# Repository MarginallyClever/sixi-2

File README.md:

# Sixi 2 Robot Arm

Sixi 2 is an open source industrial robot arm.  It is designed with six degrees of freedom and can hold 2kg at 80cm.
Some examples of it in action:

## Videos

* https://www.instagram.com/p/B56L99UnWkN/
* https://www.instagram.com/p/B6L7YMTnthS/
* https://www.instagram.com/p/B6jtXw5HbRo/

## Motivation

3D printers can print parts for themselves, but they cannot self-assemble.  The long goal of the Sixi is to build a machine that can assemble copies of itself.

When 3D printers were closed source, they started at $10k.  Makerbot and Prusa changed the game by bringing high quality open source 3D printers down to $2k.  Marginally Clever Robots, Ltd. aims to be the Prusa of robot arms.

## This repository 

This repository contains:

* The STL files from the stable version
* The bill of materials (BOM.csv)
* Issue tickets specifically related to the hardware.
* ROS package.

This repository does NOT contain:

* Assembly instructions + software guide: https://mcr.dozuki.com/c/Sixi_2_kit_Asssembly
* Robot Overlord app to simulate, drive, and test Sixi: https://github.com/MarginallyClever/Robot-Overlord-App
* Makelangelo Firmware in the Sixi's brain: https://github.com/MarginallyClever/Makelangelo-firmware

## Notes

The BOM.csv lists all the parts in the kit, most of which are off-the-shelf.  Some parts are manufactured.
	
	[LSR] laser cut
	[CNC] metal cut on a CNC mill
	[3D]  3D printed PLA plastic.

All the 3D printable parts were produced on a Prusa MK3S.  Parts are carefully designed to have a minimum of support material cleaning.
Please see STLs/STLPrintSettings.csv for recommended layer height, speed, color, etc.

The Sixi has no glue because we like operations that can be undone.

## Collaborate

We love collaborating!  Let's make great things happen together.

* Discuss the project in our Discord: https://discord.gg/p2NRZFxXbh
* For a link to the Fusion files, become one of our Patreon supporters: https://www.patreon.com/imakerobots
* See also the ROS.org wiki page: https://wiki.ros.org/Robots/Sixi

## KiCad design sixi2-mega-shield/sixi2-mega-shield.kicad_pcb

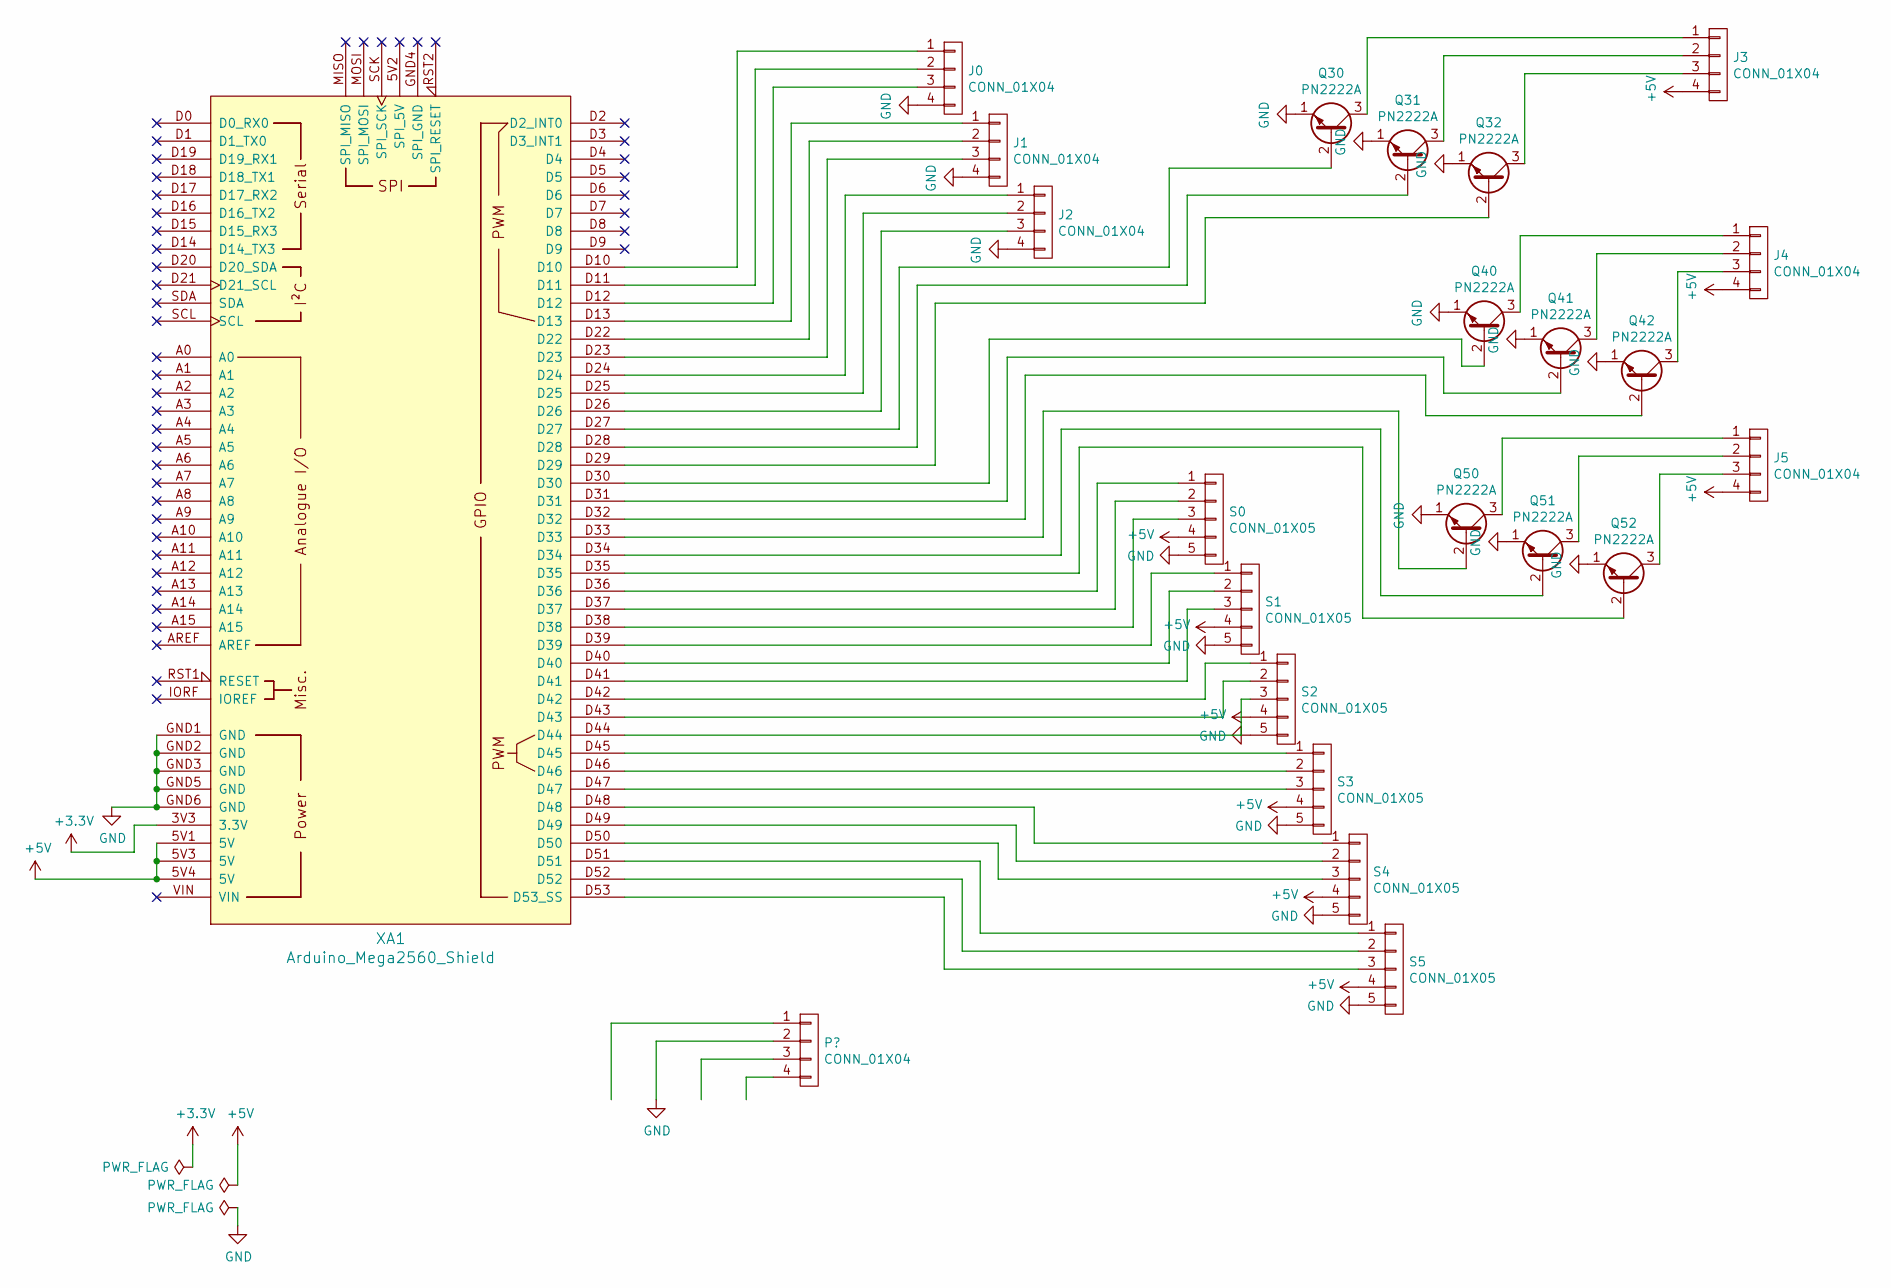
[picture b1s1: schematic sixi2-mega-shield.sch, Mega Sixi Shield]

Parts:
J0, J1, J2, J3, J4, J5: CONN_01X04; JST_XH_B4B-XH-A_1x04_P2.50mm_Vertical
Q30, Q31, Q32, Q40, Q41, Q42, Q50, Q51, Q52: PN2222A; TO-92_Inline_Wide
S0, S1, S2, S3, S4, S5: CONN_01X05; JST_XH_B5B-XH-A_1x05_P2.50mm_Vertical
XA1: Arduino_Mega2560_Shield

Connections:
+5V: J3.4, J4.4, J5.4, S0.4, S1.4, S2.4, S3.4, S4.4, S5.4, XA1.5V1 (5V), XA1.5V3 (5V), XA1.5V4 (5V)
GND: J0.4, J1.4, J2.4, Q30.1 (E), Q31.1 (E), Q32.1 (E), Q40.1 (E), Q41.1 (E), Q42.1 (E), Q50.1 (E), Q51.1 (E), Q52.1 (E), S0.5, S1.5, S2.5, S3.5, S4.5, S5.5, XA1.GND1 (GND), XA1.GND2 (GND), XA1.GND3 (GND), XA1.GND5 (GND), XA1.GND6 (GND)
unnamed: J0.1, XA1.D10
unnamed: J0.2, XA1.D11
unnamed: J0.3, XA1.D12
unnamed: J1.1, XA1.D13
unnamed: J1.2, XA1.D22
unnamed: J1.3, XA1.D23
unnamed: J2.1, XA1.D24
unnamed: J2.2, XA1.D25
unnamed: J2.3, XA1.D26
unnamed: J3.1, Q30.3 (C)
unnamed: J3.2, Q31.3 (C)
unnamed: J3.3, Q32.3 (C)
unnamed: J4.1, Q40.3 (C)
unnamed: J4.2, Q41.3 (C)
unnamed: J4.3, Q42.3 (C)
unnamed: J5.1, Q50.3 (C)
unnamed: J5.2, Q51.3 (C)
unnamed: J5.3, Q52.3 (C)
unnamed: Q30.2 (B), XA1.D27
unnamed: Q31.2 (B), XA1.D28
unnamed: Q32.2 (B), XA1.D29
unnamed: Q40.2 (B), XA1.D30
unnamed: Q41.2 (B), XA1.D31
unnamed: Q42.2 (B), XA1.D32
unnamed: Q50.2 (B), XA1.D33
unnamed: Q51.2 (B), XA1.D34
unnamed: Q52.2 (B), XA1.D35
unnamed: S0.1, XA1.D36
unnamed: S0.2, XA1.D37
unnamed: S0.3, XA1.D38
unnamed: S1.1, XA1.D39
unnamed: S1.2, XA1.D40
unnamed: S1.3, XA1.D41
unnamed: S2.1, XA1.D42
unnamed: S2.2, XA1.D43
unnamed: S2.3, XA1.D44
unnamed: S3.1, XA1.D45
unnamed: S3.2, XA1.D46
unnamed: S3.3, XA1.D47
unnamed: S4.1, XA1.D48
unnamed: S4.2, XA1.D49
unnamed: S4.3, XA1.D50
unnamed: S5.1, XA1.D51
unnamed: S5.2, XA1.D52
unnamed: S5.3, XA1.D53 (D53_SS)

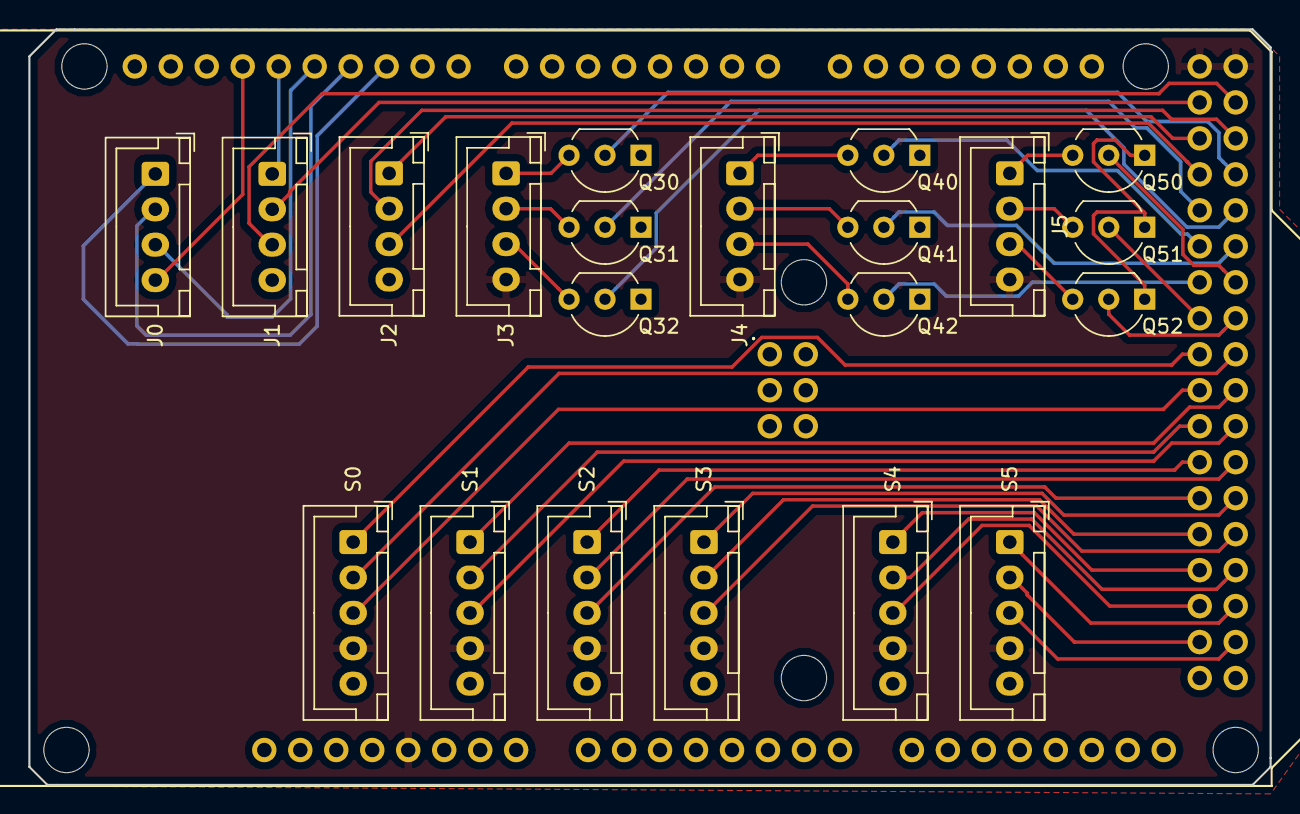
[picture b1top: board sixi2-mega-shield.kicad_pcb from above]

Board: 2 copper layers, 87.6 x 53.3 mm, 22 parts (0 on the bottom side), 47 nets.

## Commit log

2018-12-01 initial commit
    hooray!
2018-12-02 added tools
2018-12-04 updated j3 sensor mount to include letters on part models
2018-12-10 Fix for #1 + added discord link
2018-12-10 update 3Bb, added hole cut pattern for PVC tube.
2018-12-10 fixed formatting
2018-12-10 added image description
2018-12-10 formatting
2019-04-05 Update for 2019-04-04.
    Only the kicad sixi2-mega-shield is currently valid. All other files should be treated as suspect. We are working out a new process in the workshop so that they will stay up to date all the time.
2019-05-23 removed old picture.
2019-09-02 added graphs
2020-02-14 Updated STL files
2020-02-24 STL export finalized, printsetting added
2020-02-26 csv version added, lsr dxf deleted,
2020-02-26 update readme and BOM
2020-02-26 added 089
2020-03-02 Turned parts for printing
2020-03-03 shoulder cut wasn't done correctly, fixed
2020-03-03 ElbowGB 3mm Roller Fixed
2020-03-03 added Sixi2Processing demo
2020-03-03 added SKUs to STL print settings file
2020-03-03 aesthetic improvements
2020-03-03 visuals
2020-03-26 print setting csv file delimiter added
2020-07-28 added ROS package
2020-07-28 new readme image
2020-07-28 fixed inline image
2020-08-25 Aug.25th STLs update
    - Notable updates
    -- Anchor Gearbox with 3mm dowel Pins
    But all STL files has been exported anew.
2020-08-25 removing old material
2020-08-25 updated bill of materials
2020-08-28 update with buy-now for bearings
2020-09-14 renamed STL files to include SKU codes
2020-09-16 rotated for printing
2021-12-29 Update issue templates
